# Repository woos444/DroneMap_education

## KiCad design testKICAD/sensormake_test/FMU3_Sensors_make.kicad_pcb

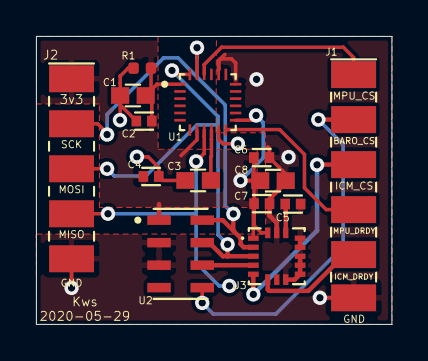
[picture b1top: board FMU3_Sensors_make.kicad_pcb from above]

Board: 2 copper layers, 19.8 x 16.0 mm, 14 parts (0 on the bottom side), 12 nets.

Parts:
C1, C3, C8: 2u2; CAPC1608X90N
C2, C4, C5, C7: 0u1; CAPC1005X55N
C6: 10nF; CAPC1005X55N
J1: Conn_01x06_Male; sensorconnect_1x6
J2: Conn_01x05; sensorconnect_1x5
R1: 220R; C_0402_1005Metric
U1: MPU-9250; QFN40P300X300X105-24N
U2: MS561101BA03-50; SON125P500X300X100-8N
U3: ICM-20602; PQFN50P300X300X80-16N

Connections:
/BARO_CS: J1.2, U2.5
/ICM_CS: J1.3, U3.5
/ICM_DRDY: J1.5, U3.6
/MPU_CS: J1.1, U1.22
/MPU_DRDY: J1.4, U1.12
/SPI_INT_MISO: J2.4, U1.9, U2.6, U3.4
/SPI_INT_MOSI: J2.3, U1.24, U2.7, U3.3
/SPI_INT_SCK: J2.2, U1.23, U2.8, U3.2
/VDD_3V3_SENSORS: C1.1, C2.1, C4.1, C6.1, C7.1, C8.1, J2.1, R1.1, U1.1, U1.8, U1.13, U2.1, U3.1, U3.16
GND: C1.2, C2.2, C3.2, C4.2, C5.2, C6.2, C7.2, C8.2, J1.6, J2.5, R1.2, U1.11, U1.18, U1.20, U2.2, U2.3, U3.8, U3.9, U3.10, U3.11, U3.12, U3.13, U3.15
unnamed: C3.1, U1.10
unnamed: C5.1, U3.14

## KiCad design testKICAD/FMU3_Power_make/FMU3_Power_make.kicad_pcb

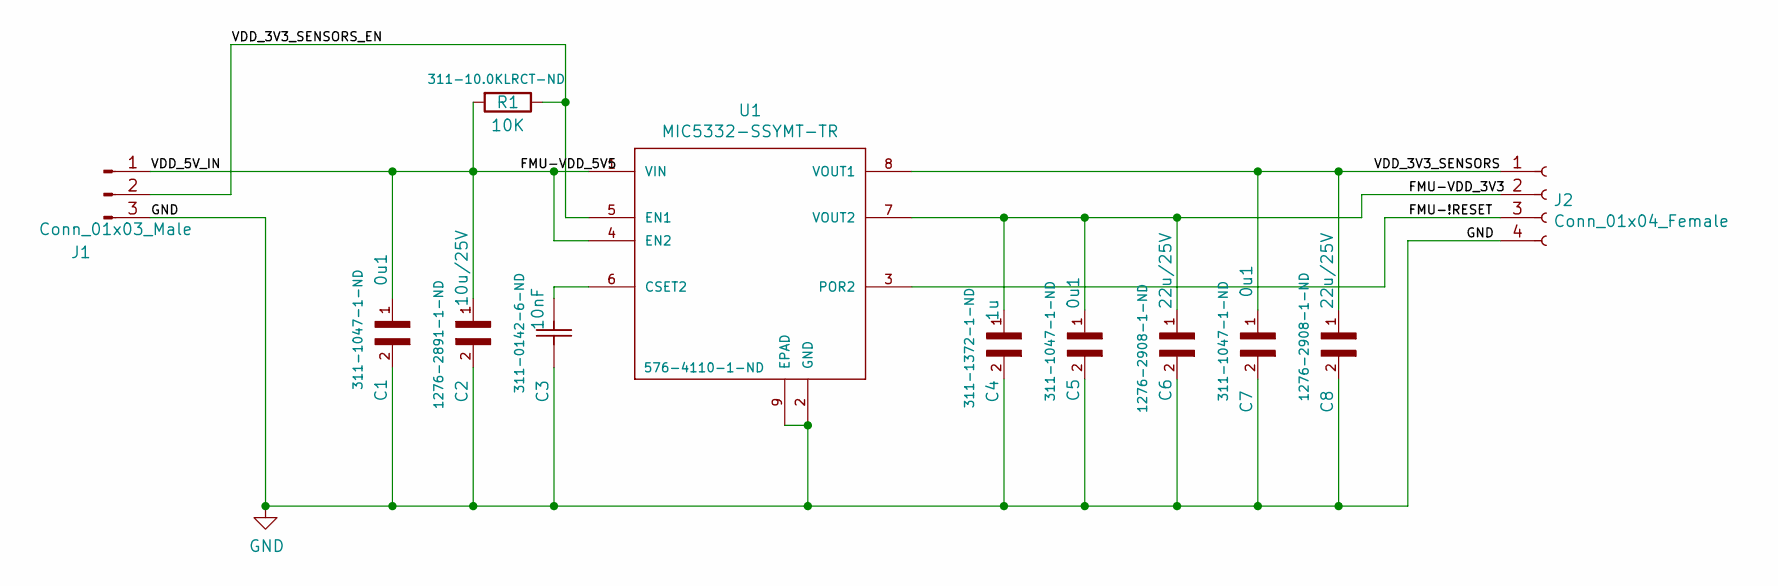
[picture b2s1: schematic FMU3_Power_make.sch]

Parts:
C1, C5, C7: 0u1; CAPC1005X55N
C2: 10u/25V; CAPC2012X135N
C3: CC0402KRX7R7BB103; CAPC1005X55N
C4: 1u; CAPC1608X90
C6, C8: 22u/25V; CAPC2012X140N
J1: Conn_01x03_Male; Conn_01x03_SMD
J2: Conn_01x04_Female; Conn_01x04_SMD
R1: 10K; RC0402FR-0710KL
U1: MIC5332-SSYMT-TR; SON50P200X200X60-9N

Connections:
/FMU-!RESET: J2.3, U1.3 (POR2)
/FMU-VDD_3V3: C4.1, C5.1, C6.1, J2.2, U1.7 (VOUT2)
/FMU-VDD_5V5: C1.1, C2.1, J1.1, R1.2, U1.1 (VIN), U1.4 (EN2)
/VDD_3V3_SENSORS: C7.1, C8.1, J2.1, U1.8 (VOUT1)
/VDD_3V3_SENSORS_EN: J1.2, R1.1, U1.5 (EN1)
GND: C1.2, C2.2, C3.2 (C2), C4.2, C5.2, C6.2, C7.2, C8.2, J1.3, J2.4, U1.2 (GND), U1.9 (EPAD)
unnamed: C3.1 (C1), U1.6 (CSET2)

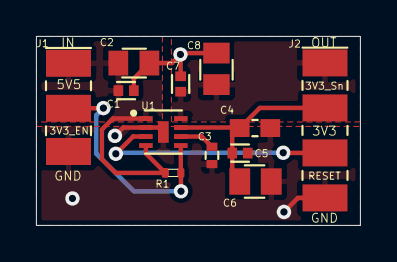
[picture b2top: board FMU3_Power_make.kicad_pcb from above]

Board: 2 copper layers, 18.0 x 10.5 mm, 12 parts (0 on the bottom side), 7 nets.

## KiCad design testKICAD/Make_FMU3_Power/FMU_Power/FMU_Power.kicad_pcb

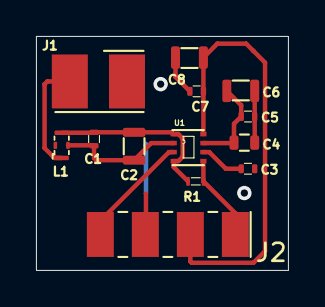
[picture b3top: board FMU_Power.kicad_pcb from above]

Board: 2 copper layers, 14.0 x 13.0 mm, 13 parts (0 on the bottom side), 8 nets.

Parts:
C1, C5, C7: 0u1; CC0402ZRY5V7BB104_1.0x0.5mm
C2: 10u/25V; CL21A106KAYNNNE_2.0x1.25mm
C3: 10n; CC0402KRX7R7BB103_1.0x0.5mm
C4: 1u; CC0603ZRY5V7BB105_1.6x0.8
C6, C8: 22u/25V; CL21A226MAQNNNE_2.0x1.25mm
J1: Conn_01x02_Male; FMU3_VDD_5V_IN_Connector
J2: Conn_01x04_Male; MIC5332_OUTPUT_Connector
L1: Kyocera KNH16C104DA5TS EMI filter; KNH16C104DA5TS_EMI_filter
R1: 10K; RC0402FR-0710KL_1.0x0.5mm
U1: MIC5332

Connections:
/FMU-!RESET: J2.4, U1.3
/FMU-VDD_3V3: C4.1, C5.1, C6.1, J2.3, U1.7
/VDD_3V3_SENSORS: C7.1, C8.1, J2.2, U1.8
/VDD_3V3_SENSORS_EN: J2.1, R1.1, U1.5
/VDD_5V_IN: J1.1, L1.1
GND: C1.2, C2.2, C3.2, C4.2, C5.2, C6.2, C7.2, C8.2, J1.2, L1.2, U1.2
unnamed: C1.1, C2.1, L1.3, R1.2, U1.1, U1.4
unnamed: C3.1, U1.6

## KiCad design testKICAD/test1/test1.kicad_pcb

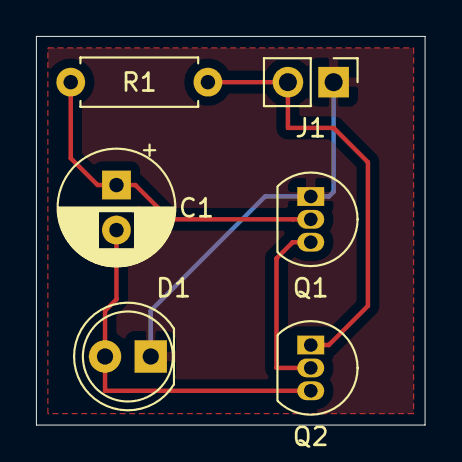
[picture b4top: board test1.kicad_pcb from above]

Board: 2 copper layers, 21.6 x 21.6 mm, 6 parts (0 on the bottom side), 5 nets.

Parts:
C1: 4.7uF; CP_Radial_D6.3mm_P2.50mm
D1: R_LED; LED_D5.0mm
J1: Conn_01x02_Male; PinHeader_1x02_P2.54mm_Vertical
Q1: 2N3904; TO-92_Inline
Q2: 2N3905; TO-92_Inline
R1: 1M; R_Axial_DIN0207_L6.3mm_D2.5mm_P7.62mm_Horizontal

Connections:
+5V: J1.2, Q2.1, R1.1
GND: D1.1, J1.1, Q1.1
unnamed: C1.1, Q1.2, R1.2
unnamed: C1.2, D1.2, Q2.3
unnamed: Q1.3, Q2.2

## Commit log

2020-05-15 commit!
2020-05-19 FMU3 Power make
2020-05-19 FMU power 수정본
2020-05-21 adding files
2020-05-22 new make FMU3_power
2020-05-25 save
2020-05-25 Parts 3D modelling
2020-05-26 FMU3_SENSORS make
2020-05-27 sensorbord add example
2020-05-28 FMU3_power gbr
2020-05-29 save Estimate
2020-06-01 Sensor board completed
2020-06-02 save sensor
2020-06-05 sensor add parth
2020-06-08 save last
